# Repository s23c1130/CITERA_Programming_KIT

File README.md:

# CITERA Programming KIT
このプロジェクトは、千葉工業大学 電子工学研究会 (CITERA)で開発・頒布されたプログラミングキットの説明書・プログラミングツール・書き込みツール等をまとめたものです。

質問などは下のGoogle Formをご利用ください<BR>
https://forms.gle/aoQnFYQyJ1tKQqx78

バグの報告や機能の追加の希望等は上のGoogle Formをご利用いただくか、Issueを立ち上げてください。

**自己責任で導入を行ってください**<BR>

## 使用できる環境・推奨環境
このプログラムは次の環境で動作確認されています。
- Windows 11 (24H2)

最低限必要な環境は以下の通りです。
- Windows 11

必須ソフトとして.NET Framework 4.8が必要です。（Windows 11には初期状態で含まれています。）
.NET Framework 4.8 が入っていない環境の場合、下のリンクから、ランタイムをダウンロード・インストールしてください。

https://dotnet.microsoft.com/ja-jp/download/dotnet-framework/net48

（Windows 7以降の環境であれば動作すると思われますが、OSサポート終了のため推奨しません）

## プログラミング・書き込みツールの導入方法
ダウンロードしてから展開するだけでプログラミング・書き込みできるようになるReleaseファイルを配布しています。

矢印の先にReleasesがあります。これをクリックします。

Assetsにある`CITERA_Program_X.X.X.zip`をクリックし、ダウンロードします。

エクスプローラーの標準機能や7-Zip等のソフトを用いてZIPファイルを展開してください。

Windows エクスプローラーの標準機能を利用している場合は、展開ボタンを押してください。このとき、展開先のパスに2バイト文字（ひらがなや漢字などの日本語文字）が入っていないことを確認してください。（外部ツールの仕様により正常に動作しなくなります）

展開が完了すると次のような画面になります。

`CITERA_Programming_Kit_CWriter`にはマイコンに書き込むためのプログラムが入っています。<BR>
`BlocklyDuino-v2`にはプログラミングツールが入っています。

次にドライバの書き換えに進んでください。

## ドライバの書き換え
**この作業は管理者権限が必要です**<BR>
**Zadigは手順を間違えるとPCが不調になったりします。必ずこの手順通りに行ってください**<BR>

プログラムをマイコンに書き込む時、ドライバを書き換える必要があります。

準備中...

## プログラミングツールの説明
プログラミングツールの起動の仕方

まず、BlocklyDuino-v2のフォルダをダブルクリックで開いてください。

「index.html」もしくは「index」をダブルクリックで開いてください。
もし、使用するソフトウェアを聞かれた場合、「Microsoft Edge」もしくは「Google Chrome」を選択してください。

使用するボードの選択をするために、丸の箇所をクリックしてボードリストを開きます。

使用するボードはリストの下にあるので、下にスクロールします。

丸の箇所をクリックして「citera_board」を選択します。

ボードの選択後、BlocklyDuino-v2の表示の更新をします。

正常にボードの選択が出来た場合。表示の更新後、左側のツールボックスはこのような表示になります。「Arduino」等のツールボックスが表示されている場合、ボードの選択が正常に出来ていません。再度、ボードの選択をしてください。選択が完了している場合、以下のように、「citera_board」が黄色にハイライトされます。

プログラミングの例：3分タイマー

## 書き込みツールの説明
PCからマイコンボードにプログラムを書き込む方法について説明します。

1. マイコンボードとPCをUSBケーブルで接続します。
2. 電源をONにして、WRITEモードにスイッチをスライドさせます。
3. RESETボタンを押します。（画像では赤いボタンがリセットボタン）

これでマイコンボードは書き込みモードになりました。

次に、プログラムを書き込みます。

`CITERA_Programming_KIT_CWriter`フォルダを開きます

`CH32V203_USB_CBT.exe`(または`CH32V203_USB_CBT`)を実行してください。

## ライセンス
各ツール・設計図のライセンスについては、各フォルダに含まれている`README.md`をご参照ください。

`ProgrammingKit_回路図.pdf`<BR>
`ProgrammingKit_DotMatrix_回路図.pdf`<BR>
`ProgrammingKit_Car_回路図.pdf`<BR>
の著作権は CITERA また 23C1130 が保持しています。また、この回路図データは Creative Commons Attribution 4.0 International (CC BY 4.0) ライセンスの下で提供されています。
https://creativecommons.org/licenses/by/4.0/

## 外部ツールについて
### Zadig
このプロジェクトにはUSBドライバインストールツール Zadigを使用しています。<BR>
またReleaseにバイナリファイル（実行ファイル）が同梱されています。<BR>
- ライセンス:GPLv3
- ソースコード:https://github.com/pbatard/libwdi
- 公式HP:https://zadig.akeo.ie/

ZadigはGPLv3ライセンスの条件に基づいて再配布されています。<BR>
詳しくは`LICENSE/GPL-3.0.txt`をご参照ください。
### wchisp
このプロジェクトにはWCH ISP Tool wchispを使用しています。<BR>
またReleaseにバイナリファイル（実行ファイル）が同梱されています。<BR>
- ライセンス:GPLv2
- ソースコード:https://github.com/ch32-rs/wchisp
- バイナリコード配布先:https://github.com/ch32-rs/wchisp/releases/

wchispはGPLv2ライセンスの条件に基づいて再配布されています。<BR>
詳しくは`LICENSE/GPL-2.0.txt`をご参照ください。

### xPack RISC-V Embedded GCC
このプロジェクトにはxPack GNU RISC-V Embedded GCCを使用しています。<BR>
またReleaseにバイナリファイル（実行ファイル）が同梱されています。<BR>
- ライセンス:GPLv3 with Runtime Exception + MITライセンス
- ソースコード:https://github.com/openwch/risc-none-embed-gcc
- バイナリコード配布先:https://github.com/openwch/risc-none-embed-gcc/releases

xPack GNU RISC-V Embedded GCCはMITライセンスの条件に基づいて再配布されています。<BR>
詳しくは`LICENSE/MIT.txt`をご参照ください。
また、GPLv3 with Runtime Exceptionの条件に基づいて再配布されています。<BR>
詳しくは`LICENSE/gcc-exception-3.1.txt`をご参照ください。

### BusyBox-w32
このプロジェクトにはBusyBox-w32を使用しています。<BR>
またReleaseにバイナリファイル（実行ファイル）が同梱されています。<BR>
- ライセンス:GPLv2
- ソースコード:https://github.com/rmyorston/busybox-w32
- 公式HP:https://frippery.org/busybox/

BusyBox-w32はGPLv2ライセンスの条件に基づいて再配布されています。<BR>
詳しくは`LICENSE/GPL-2.0.txt`をご参照ください。

### GNU Make
このプロジェクトにはGNU makeを使用しています。<BR>
またReleaseにバイナリファイル（実行ファイル）が同梱されています。<BR>
- ライセンス:GPLv3
- ソースコード入手先/公式HP:https://www.gnu.org/software/make/

GNU MakeはGPLv2ライセンスの条件に基づいて再配布されています。<BR>
詳しくは`LICENSE/GPL-3.0.txt`をご参照ください。

これらのソフトウェアの開発者に感謝いたします。

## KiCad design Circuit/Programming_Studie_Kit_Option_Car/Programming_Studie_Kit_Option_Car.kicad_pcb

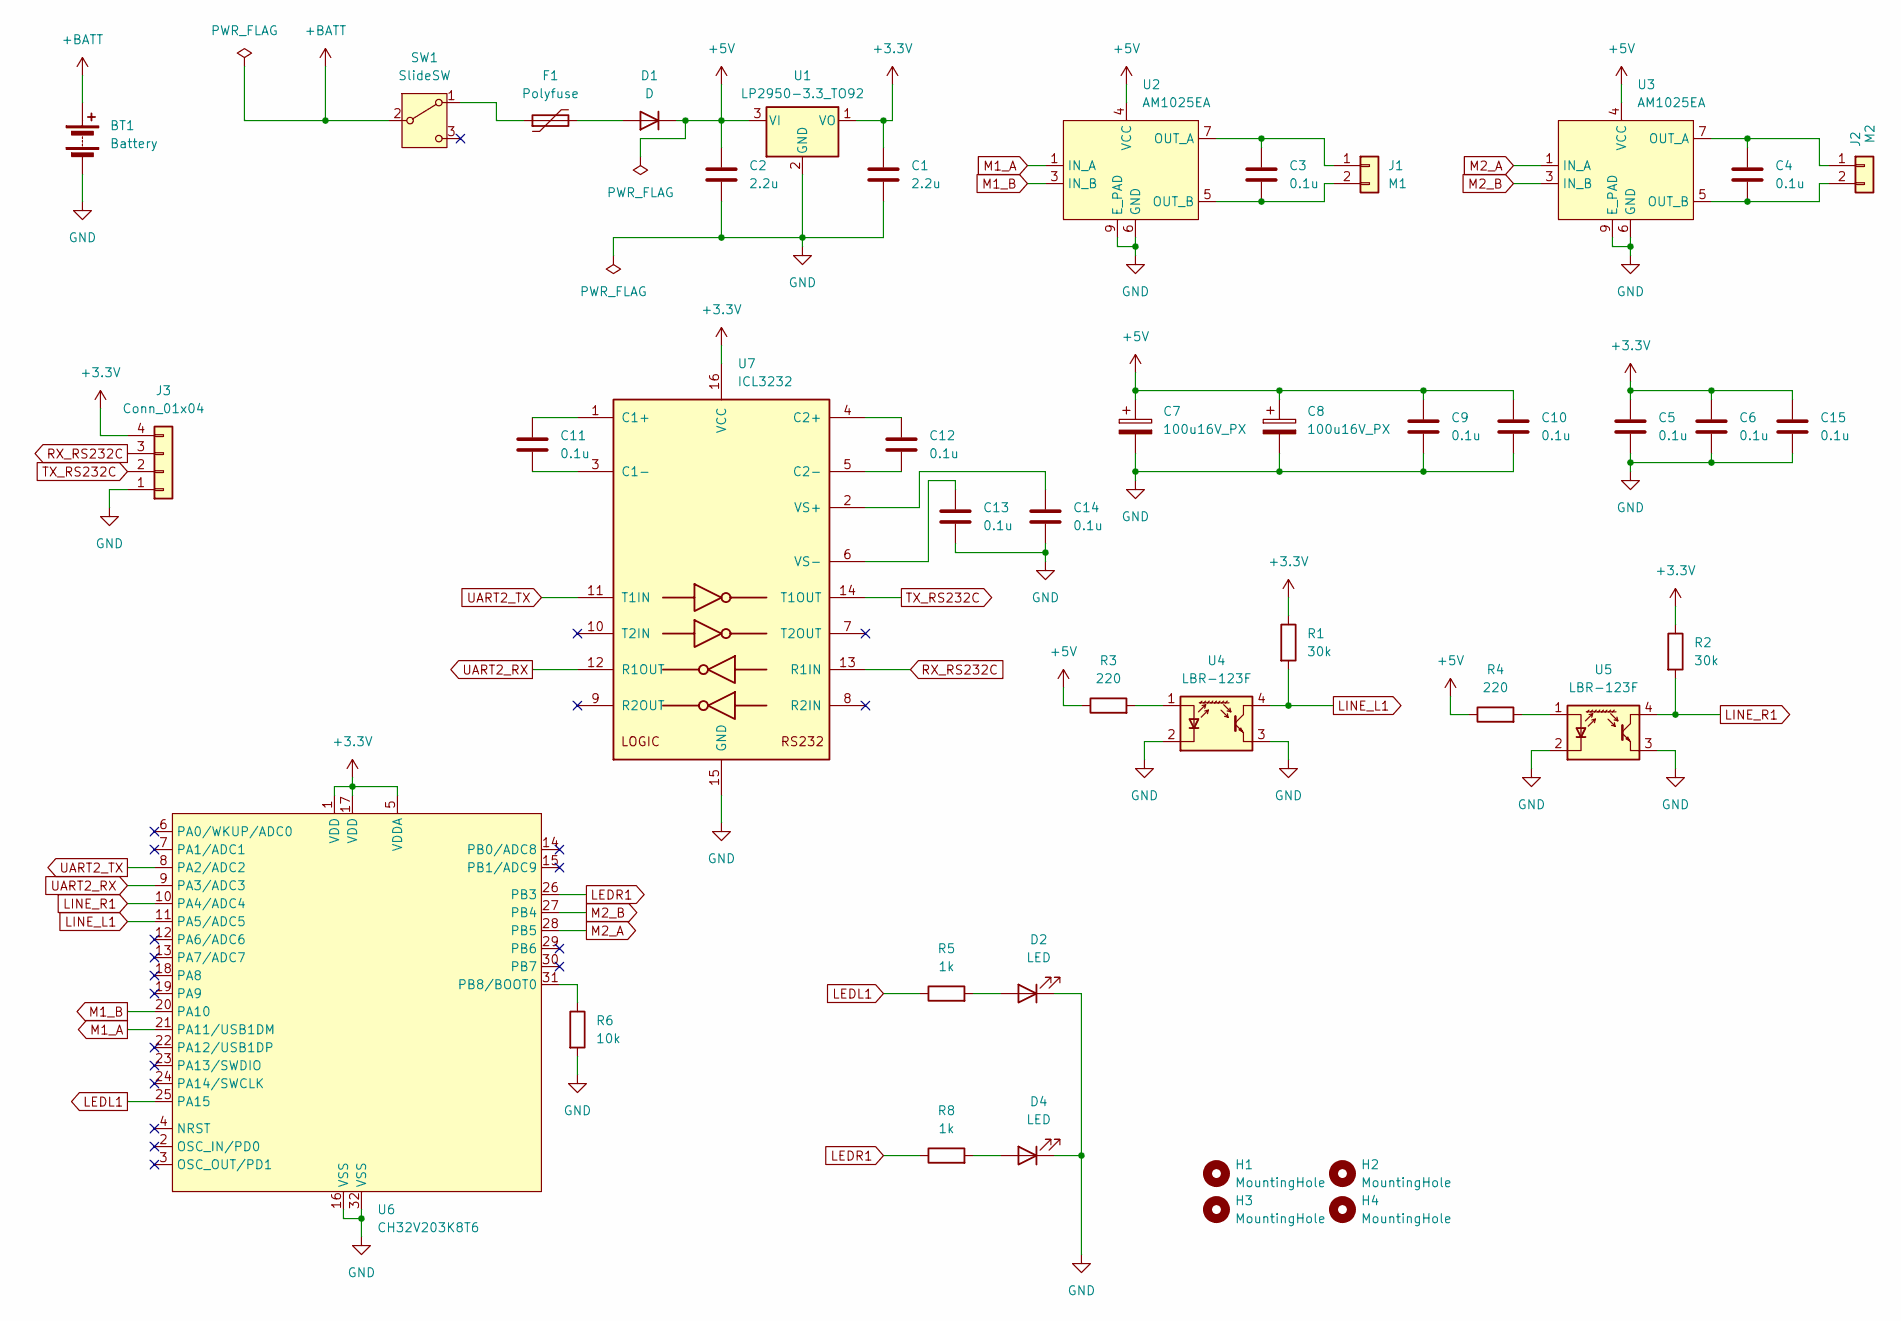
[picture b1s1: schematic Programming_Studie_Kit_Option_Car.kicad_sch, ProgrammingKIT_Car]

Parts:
BT1: Battery; JST_XH_B2B-XH-A_1x02_P2.50mm_Vertical
C1, C2: 2.2u; C_0603_1608Metric_Pad1.08x0.95mm_HandSolder
C3, C4, C5, C6, C9, C10, C11, C12, C13, C14, C15: 0.1u; C_0603_1608Metric_Pad1.08x0.95mm_HandSolder
C7, C8: 100u16V_PX; C_Radial_D5.0mm_H11.0mm_P2.00mm
D1: D; D_DO-41_SOD81_P5.08mm_Vertical_KathodeUp
D2, D4: LED; LED_D3.0mm
F1: Polyfuse; R_1_6W
H1, H2, H3, H4: MountingHole; MountingHole_3.2mm_M3
J1: M1; JST_XH_B2B-XH-A_1x02_P2.50mm_Vertical
J2: M2; JST_XH_B2B-XH-A_1x02_P2.50mm_Vertical
J3: Conn_01x04; JST_PH_B4B-PH-K_1x04_P2.00mm_Vertical
R1, R2: 30k; R_0603_1608Metric_Pad0.98x0.95mm_HandSolder
R3, R4: 220; R_0603_1608Metric_Pad0.98x0.95mm_HandSolder
R5, R8: 1k; R_0603_1608Metric_Pad0.98x0.95mm_HandSolder
R6: 10k; R_0603_1608Metric_Pad0.98x0.95mm_HandSolder
SW1: SlideSW; SW_SlideSW_3Pin_P2.54
U1: LP2950-3.3_TO92; TO-92_Inline
U2, U3: AM1025EA; SOP-8_3.76x4.96mm_P1.27mm_ThermalPAD
U4, U5: LBR-123F
U6: CH32V203K8T6; LQFP-32_7x7mm_P0.8mm
U7: ICL3232; TSSOP-16_4.4x5mm_P0.65mm

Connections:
+3.3V: C1.1, C5.1, C6.1, C15.1, J3.4, R1.1, R2.1, U1.1 (VO), U6.1 (VDD), U6.5 (VDDA), U6.17 (VDD), U7.16 (VCC)
+5V: C2.1, C7.1, C8.1, C9.1, C10.1, D1.1 (K), R3.1, R4.1, U1.3 (VI), U2.4 (VCC), U3.4 (VCC)
+BATT: BT1.1 (+), SW1.2 (B)
GND: BT1.2 (-), C1.2, C2.2, C5.2, C6.2, C7.2, C8.2, C9.2, C10.2, C13.2, C14.2, C15.2, D2.1 (K), D4.1 (K), J3.1, R6.2, U1.2 (GND), U2.6 (GND), U2.9 (E_PAD), U3.6 (GND), U3.9 (E_PAD), U4.2 (K), U4.3 (E), U5.2 (K), U5.3 (E), U6.16 (VSS), U6.32 (VSS), U7.15 (GND)
LEDL1: R5.1, U6.25 (PA15)
LEDR1: R8.1, U6.26 (PB3)
LINE_L1: R1.2, U4.4 (C), U6.11 (PA5/ADC5)
LINE_R1: R2.2, U5.4 (C), U6.10 (PA4/ADC4)
M1_A: U2.1 (IN_A), U6.21 (PA11/USB1DM)
M1_B: U2.3 (IN_B), U6.20 (PA10)
M2_A: U3.1 (IN_A), U6.28 (PB5)
M2_B: U3.3 (IN_B), U6.27 (PB4)
unnamed: D1.2 (A), F1.2
unnamed: D2.2 (A), R5.2
unnamed: D4.2 (A), R8.2
unnamed: C3.1, J1.1, U2.7 (OUT_A)
unnamed: C3.2, J1.2, U2.5 (OUT_B)
unnamed: C4.1, J2.1, U3.7 (OUT_A)
unnamed: C4.2, J2.2, U3.5 (OUT_B)
unnamed: F1.1, SW1.1 (A)
unnamed: R3.2, U4.1 (A)
unnamed: R4.2, U5.1 (A)
unnamed: R6.1, U6.31 (PB8/BOOT0)
unnamed: C11.1, U7.1 (C1+)
unnamed: C11.2, U7.3 (C1-)
unnamed: C12.1, U7.4 (C2+)
unnamed: C12.2, U7.5 (C2-)
unnamed: C14.1, U7.2 (VS+)
unnamed: C13.1, U7.6 (VS-)
RX_RS232C: J3.3, U7.13 (R1IN)
TX_RS232C: J3.2, U7.14 (T1OUT)
UART2_RX: U6.9 (PA3/ADC3), U7.12 (R1OUT)
UART2_TX: U6.8 (PA2/ADC2), U7.11 (T1IN)

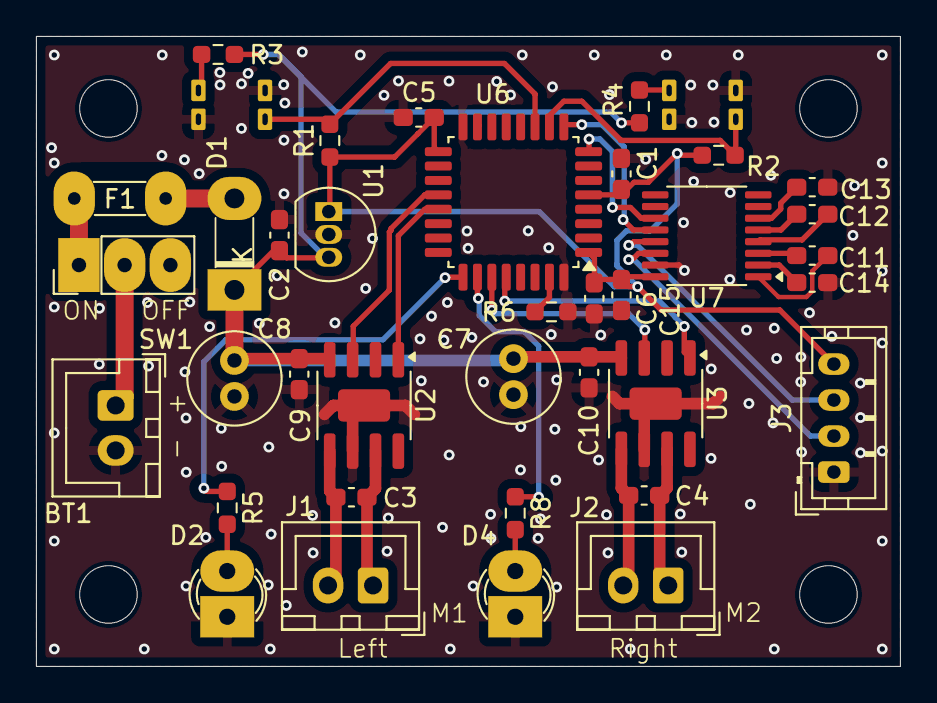
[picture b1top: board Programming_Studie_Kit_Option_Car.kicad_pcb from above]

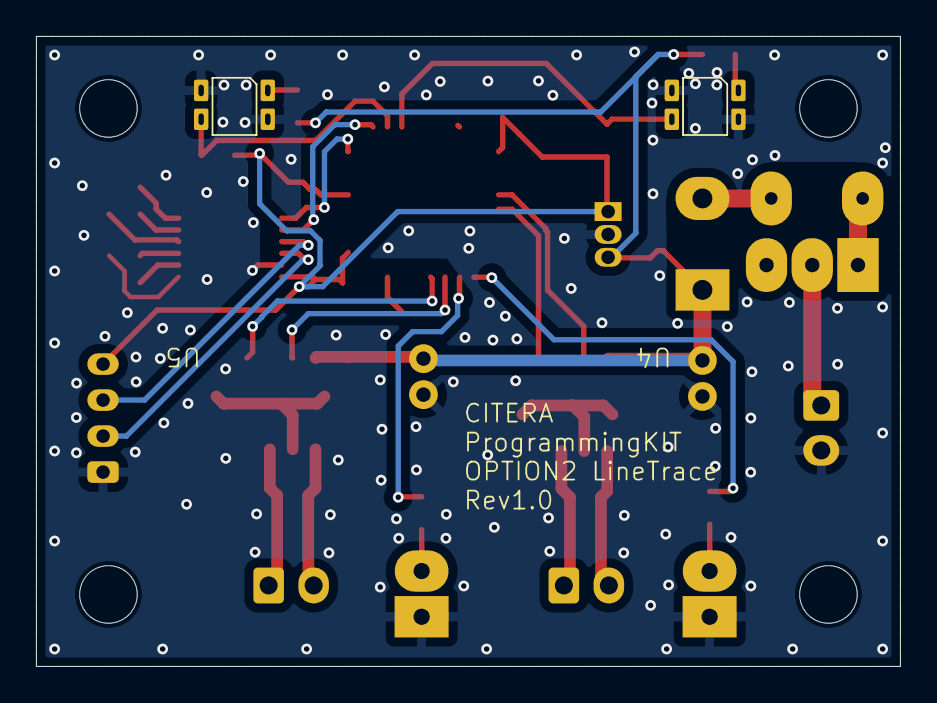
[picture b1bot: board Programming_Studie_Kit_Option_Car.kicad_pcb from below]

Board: 2 copper layers, 48.0 x 35.0 mm, 42 parts (2 on the bottom side), 33 nets.

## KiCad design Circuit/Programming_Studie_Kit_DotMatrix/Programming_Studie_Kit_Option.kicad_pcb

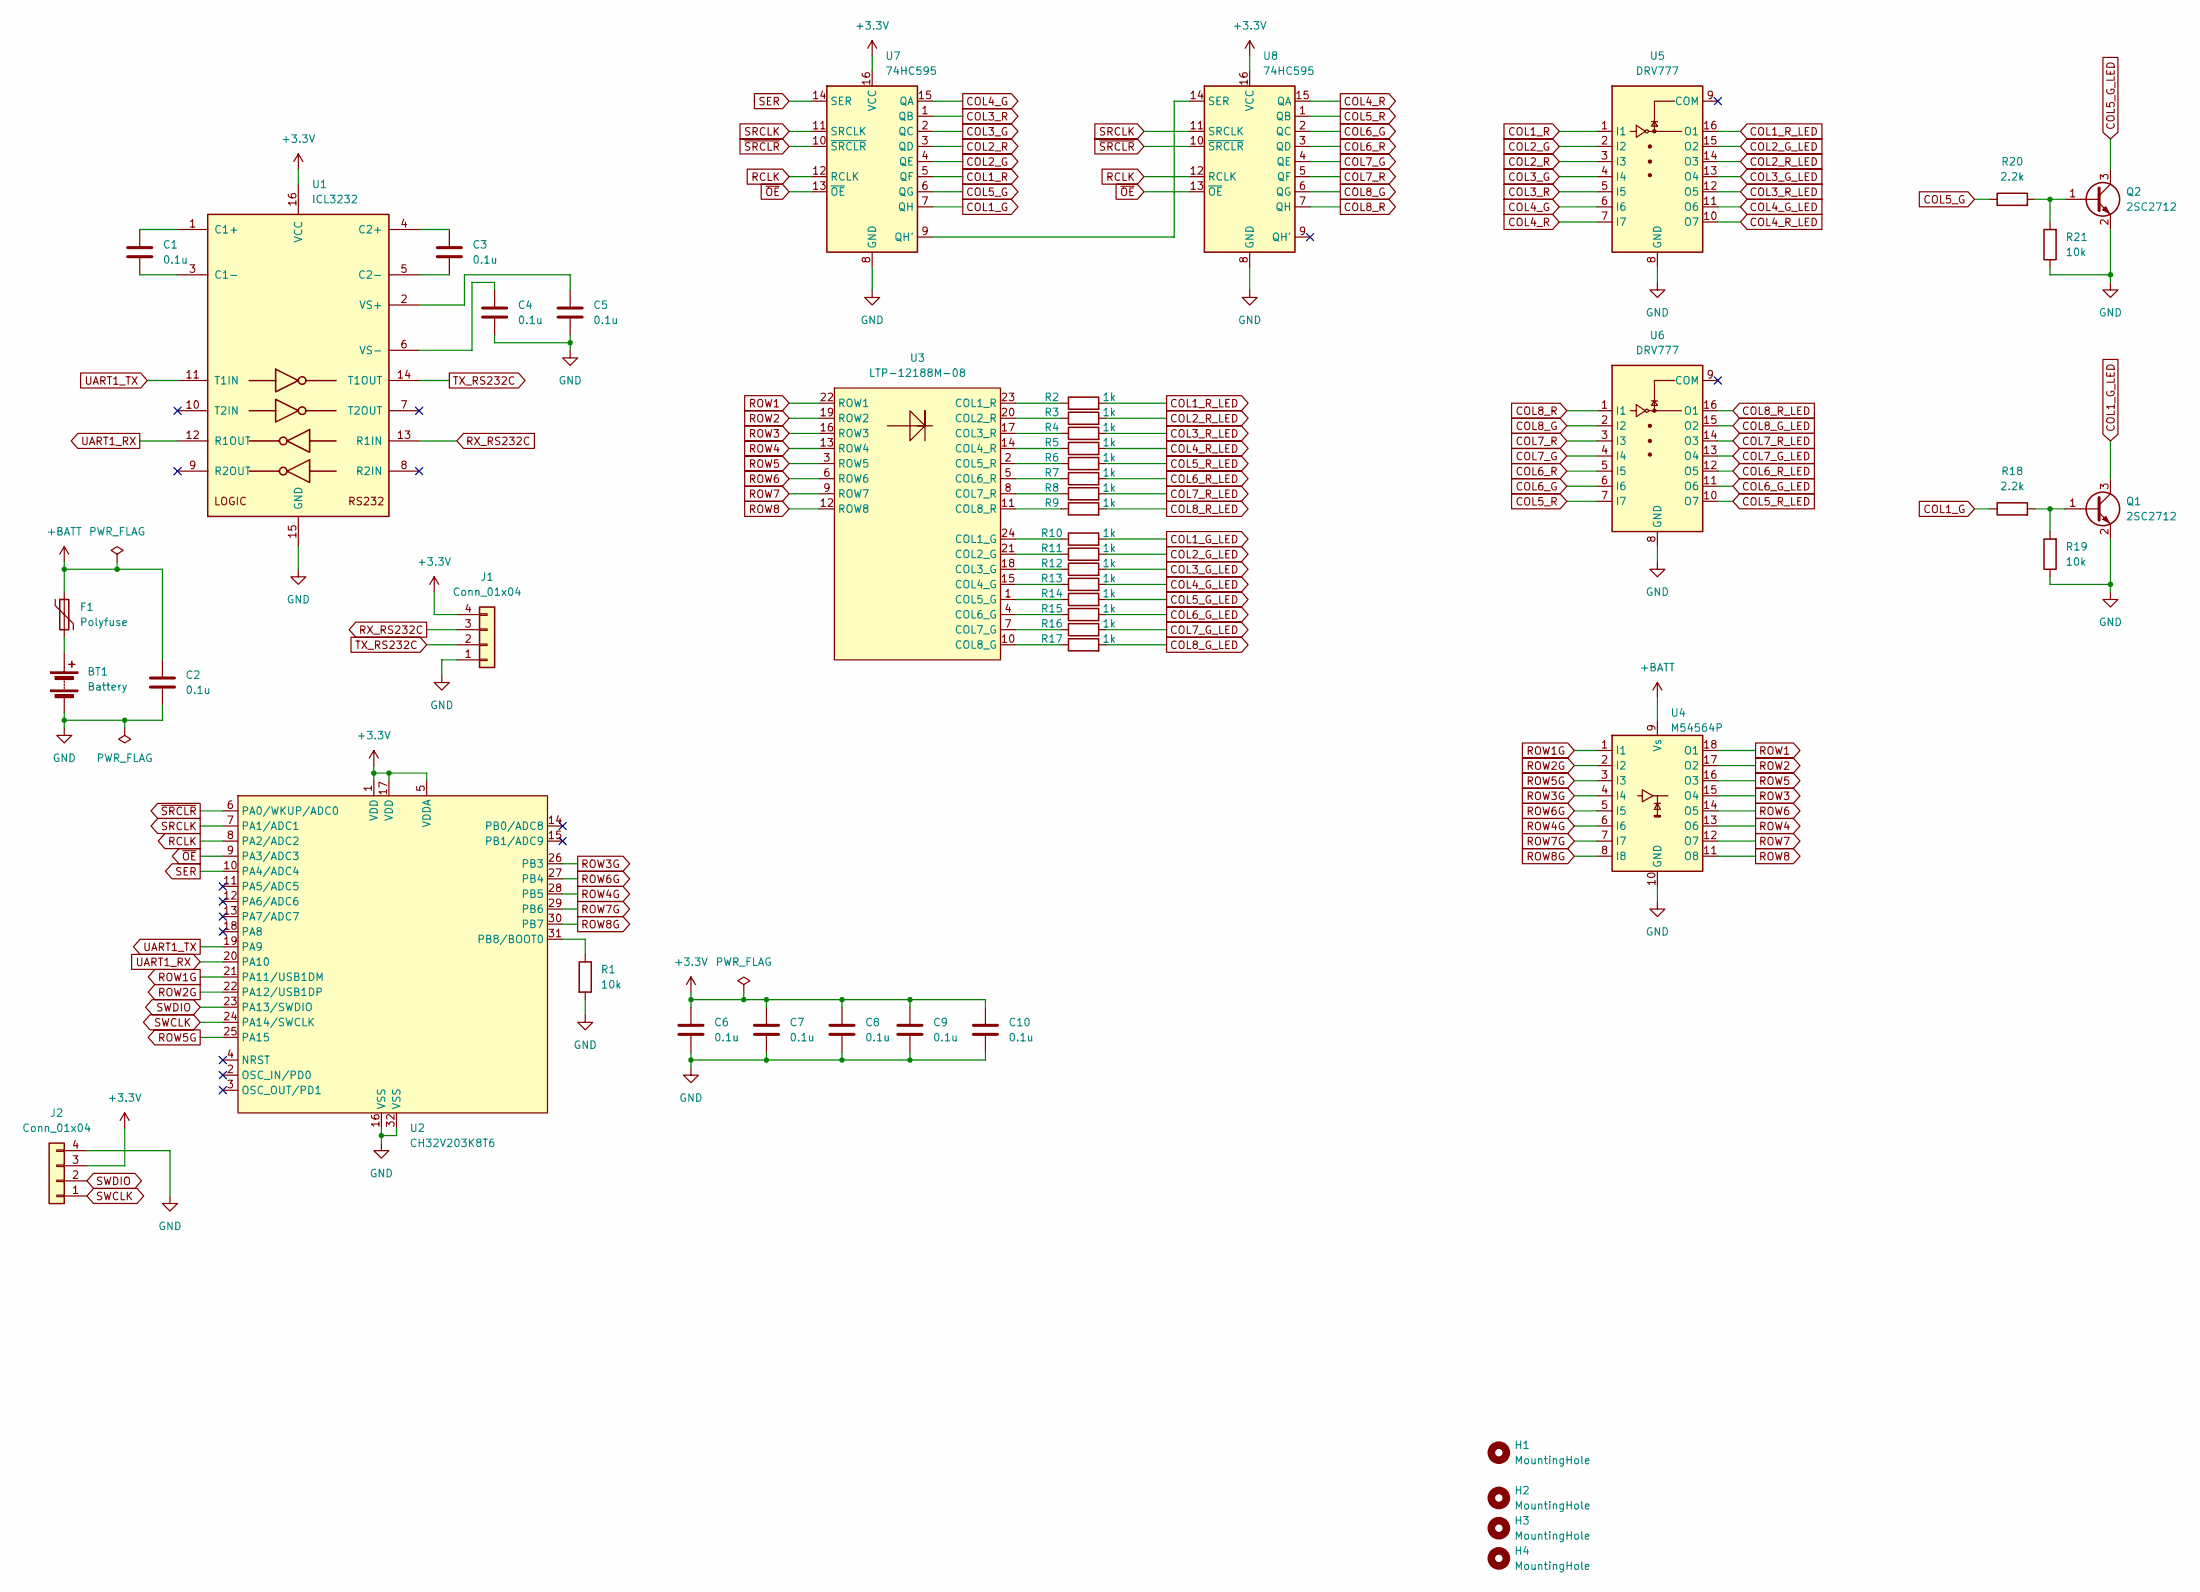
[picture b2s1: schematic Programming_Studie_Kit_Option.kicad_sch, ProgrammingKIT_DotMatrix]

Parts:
BT1: Battery; JST_XH_B2B-XH-A_1x02_P2.50mm_Vertical
C1, C2, C3, C4, C5, C6, C7, C8, C9, C10: 0.1u; C_0603_1608Metric_Pad1.08x0.95mm_HandSolder
F1: Polyfuse; R_1_6W
H1, H2, H3, H4: MountingHole; MountingHole_3.2mm_M3
J1: Conn_01x04; JST_PH_B4B-PH-K_1x04_P2.00mm_Vertical
J2: Conn_01x04; PinHeader_1x04_Program
Q1, Q2: 2SC2712; SOT-23-3
R1, R19, R21: 10k; R_0603_1608Metric_Pad0.98x0.95mm_HandSolder
R2, R3, R4, R5, R6, R7, R8, R9, R10, R11, R12, R13, R14, R15, R16, R17: 1k; R_0603_1608Metric_Pad0.98x0.95mm_HandSolder
R18, R20: 2.2k; R_0603_1608Metric_Pad0.98x0.95mm_HandSolder
U1: ICL3232; TSSOP-16_4.4x5mm_P0.65mm
U2: CH32V203K8T6; LQFP-32_7x7mm_P0.8mm
U3: LTP-12188M-08
U4: M54564P; DIP-18_W7.62mm_LongPads
U5, U6: DRV777; SOIC-16_3.9x9.9mm_P1.27mm
U7, U8: 74HC595; SOP-16_4.55x10.3mm_P1.27mm

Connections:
+3.3V: C6.1, C7.1, C8.1, C9.1, C10.1, J1.4, J2.3, U1.16 (VCC), U2.1 (VDD), U2.5 (VDDA), U2.17 (VDD), U7.16 (VCC), U8.16 (VCC)
+BATT: C2.1, F1.1, U4.9 (Vs)
COL1_G: R18.1, U7.7 (QH)
COL1_G_LED: Q1.3 (C), R10.2
COL1_R: U5.1 (I1), U7.5 (QF)
COL1_R_LED: R2.2, U5.16 (O1)
COL2_G: U5.2 (I2), U7.4 (QE)
COL2_G_LED: R11.2, U5.15 (O2)
COL2_R: U5.3 (I3), U7.3 (QD)
COL2_R_LED: R3.2, U5.14 (O3)
COL3_G: U5.4 (I4), U7.2 (QC)
COL3_G_LED: R12.2, U5.13 (O4)
COL3_R: U5.5 (I5), U7.1 (QB)
COL3_R_LED: R4.2, U5.12 (O5)
COL4_G: U5.6 (I6), U7.15 (QA)
COL4_G_LED: R13.2, U5.11 (O6)
COL4_R: U5.7 (I7), U8.15 (QA)
COL4_R_LED: R5.2, U5.10 (O7)
COL5_G: R20.1, U7.6 (QG)
COL5_G_LED: Q2.3 (C), R14.2
COL5_R: U6.7 (I7), U8.1 (QB)
COL5_R_LED: R6.2, U6.10 (O7)
COL6_G: U6.6 (I6), U8.2 (QC)
COL6_G_LED: R15.2, U6.11 (O6)
COL6_R: U6.5 (I5), U8.3 (QD)
COL6_R_LED: R7.2, U6.12 (O5)
COL7_G: U6.4 (I4), U8.4 (QE)
COL7_G_LED: R16.2, U6.13 (O4)
COL7_R: U6.3 (I3), U8.5 (QF)
COL7_R_LED: R8.2, U6.14 (O3)
COL8_G: U6.2 (I2), U8.6 (QG)
COL8_G_LED: R17.2, U6.15 (O2)
COL8_R: U6.1 (I1), U8.7 (QH)
COL8_R_LED: R9.2, U6.16 (O1)
GND: BT1.2 (-), C2.2, C4.2, C5.2, C6.2, C7.2, C8.2, C9.2, C10.2, J1.1, J2.4, Q1.2 (E), Q2.2 (E), R1.2, R19.1, R21.1, U1.15 (GND), U2.16 (VSS), U2.32 (VSS), U4.10 (GND), U5.8 (GND), U6.8 (GND), U7.8 (GND), U8.8 (GND)
unnamed: BT1.1 (+), F1.2
unnamed: Q1.1 (B), R18.2, R19.2
unnamed: Q2.1 (B), R20.2, R21.2
unnamed: C1.1, U1.1 (C1+)
unnamed: C1.2, U1.3 (C1-)
unnamed: C3.1, U1.4 (C2+)
unnamed: C3.2, U1.5 (C2-)
unnamed: C5.1, U1.2 (VS+)
unnamed: C4.1, U1.6 (VS-)
unnamed: R1.1, U2.31 (PB8/BOOT0)
unnamed: R10.1, U3.24 (COL1_G)
unnamed: R2.1, U3.23 (COL1_R)
unnamed: R11.1, U3.21 (COL2_G)
unnamed: R3.1, U3.20 (COL2_R)
unnamed: R12.1, U3.18 (COL3_G)
unnamed: R4.1, U3.17 (COL3_R)
unnamed: R13.1, U3.15 (COL4_G)
unnamed: R5.1, U3.14 (COL4_R)
unnamed: R14.1, U3.1 (COL5_G)
unnamed: R6.1, U3.2 (COL5_R)
unnamed: R15.1, U3.4 (COL6_G)
unnamed: R7.1, U3.5 (COL6_R)
unnamed: R16.1, U3.7 (COL7_G)
unnamed: R8.1, U3.8 (COL7_R)
unnamed: R17.1, U3.10 (COL8_G)
unnamed: R9.1, U3.11 (COL8_R)
unnamed: U7.9 (QH'), U8.14 (SER)
RCLK: U2.8 (PA2/ADC2), U7.12 (RCLK), U8.12 (RCLK)
ROW1: U3.22 (ROW1), U4.18 (O1)
ROW1G: U2.21 (PA11/USB1DM), U4.1 (I1)
ROW2: U3.19 (ROW2), U4.17 (O2)
ROW2G: U2.22 (PA12/USB1DP), U4.2 (I2)
ROW3: U3.16 (ROW3), U4.15 (O4)
ROW3G: U2.26 (PB3), U4.4 (I4)
ROW4: U3.13 (ROW4), U4.13 (O6)
ROW4G: U2.28 (PB5), U4.6 (I6)
ROW5: U3.3 (ROW5), U4.16 (O3)
ROW5G: U2.25 (PA15), U4.3 (I3)
ROW6: U3.6 (ROW6), U4.14 (O5)
ROW6G: U2.27 (PB4), U4.5 (I5)
ROW7: U3.9 (ROW7), U4.12 (O7)
ROW7G: U2.29 (PB6), U4.7 (I7)
ROW8: U3.12 (ROW8), U4.11 (O8)
ROW8G: U2.30 (PB7), U4.8 (I8)
RX_RS232C: J1.3, U1.13 (R1IN)
SER: U2.10 (PA4/ADC4), U7.14 (SER)
SRCLK: U2.7 (PA1/ADC1), U7.11 (SRCLK), U8.11 (SRCLK)
SWCLK: J2.1, U2.24 (PA14/SWCLK)
SWDIO: J2.2, U2.23 (PA13/SWDIO)
TX_RS232C: J1.2, U1.14 (T1OUT)
UART1_RX: U1.12 (R1OUT), U2.20 (PA10)
UART1_TX: U1.11 (T1IN), U2.19 (PA9)
~OE: U2.9 (PA3/ADC3), U7.13 (~OE), U8.13 (~OE)
~SRCLR: U2.6 (PA0/WKUP/ADC0), U7.10 (~SRCLR), U8.10 (~SRCLR)

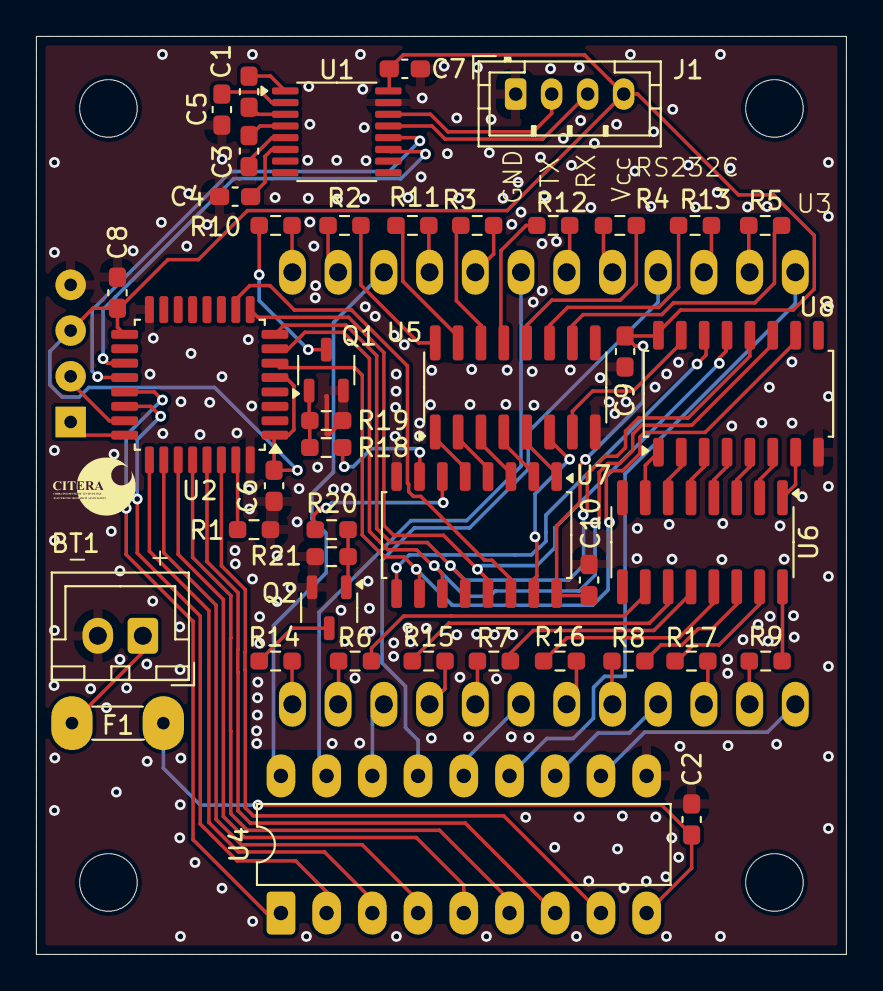
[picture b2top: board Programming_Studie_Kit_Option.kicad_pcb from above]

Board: 2 copper layers, 45.0 x 51.0 mm, 49 parts (1 on the bottom side), 89 nets.

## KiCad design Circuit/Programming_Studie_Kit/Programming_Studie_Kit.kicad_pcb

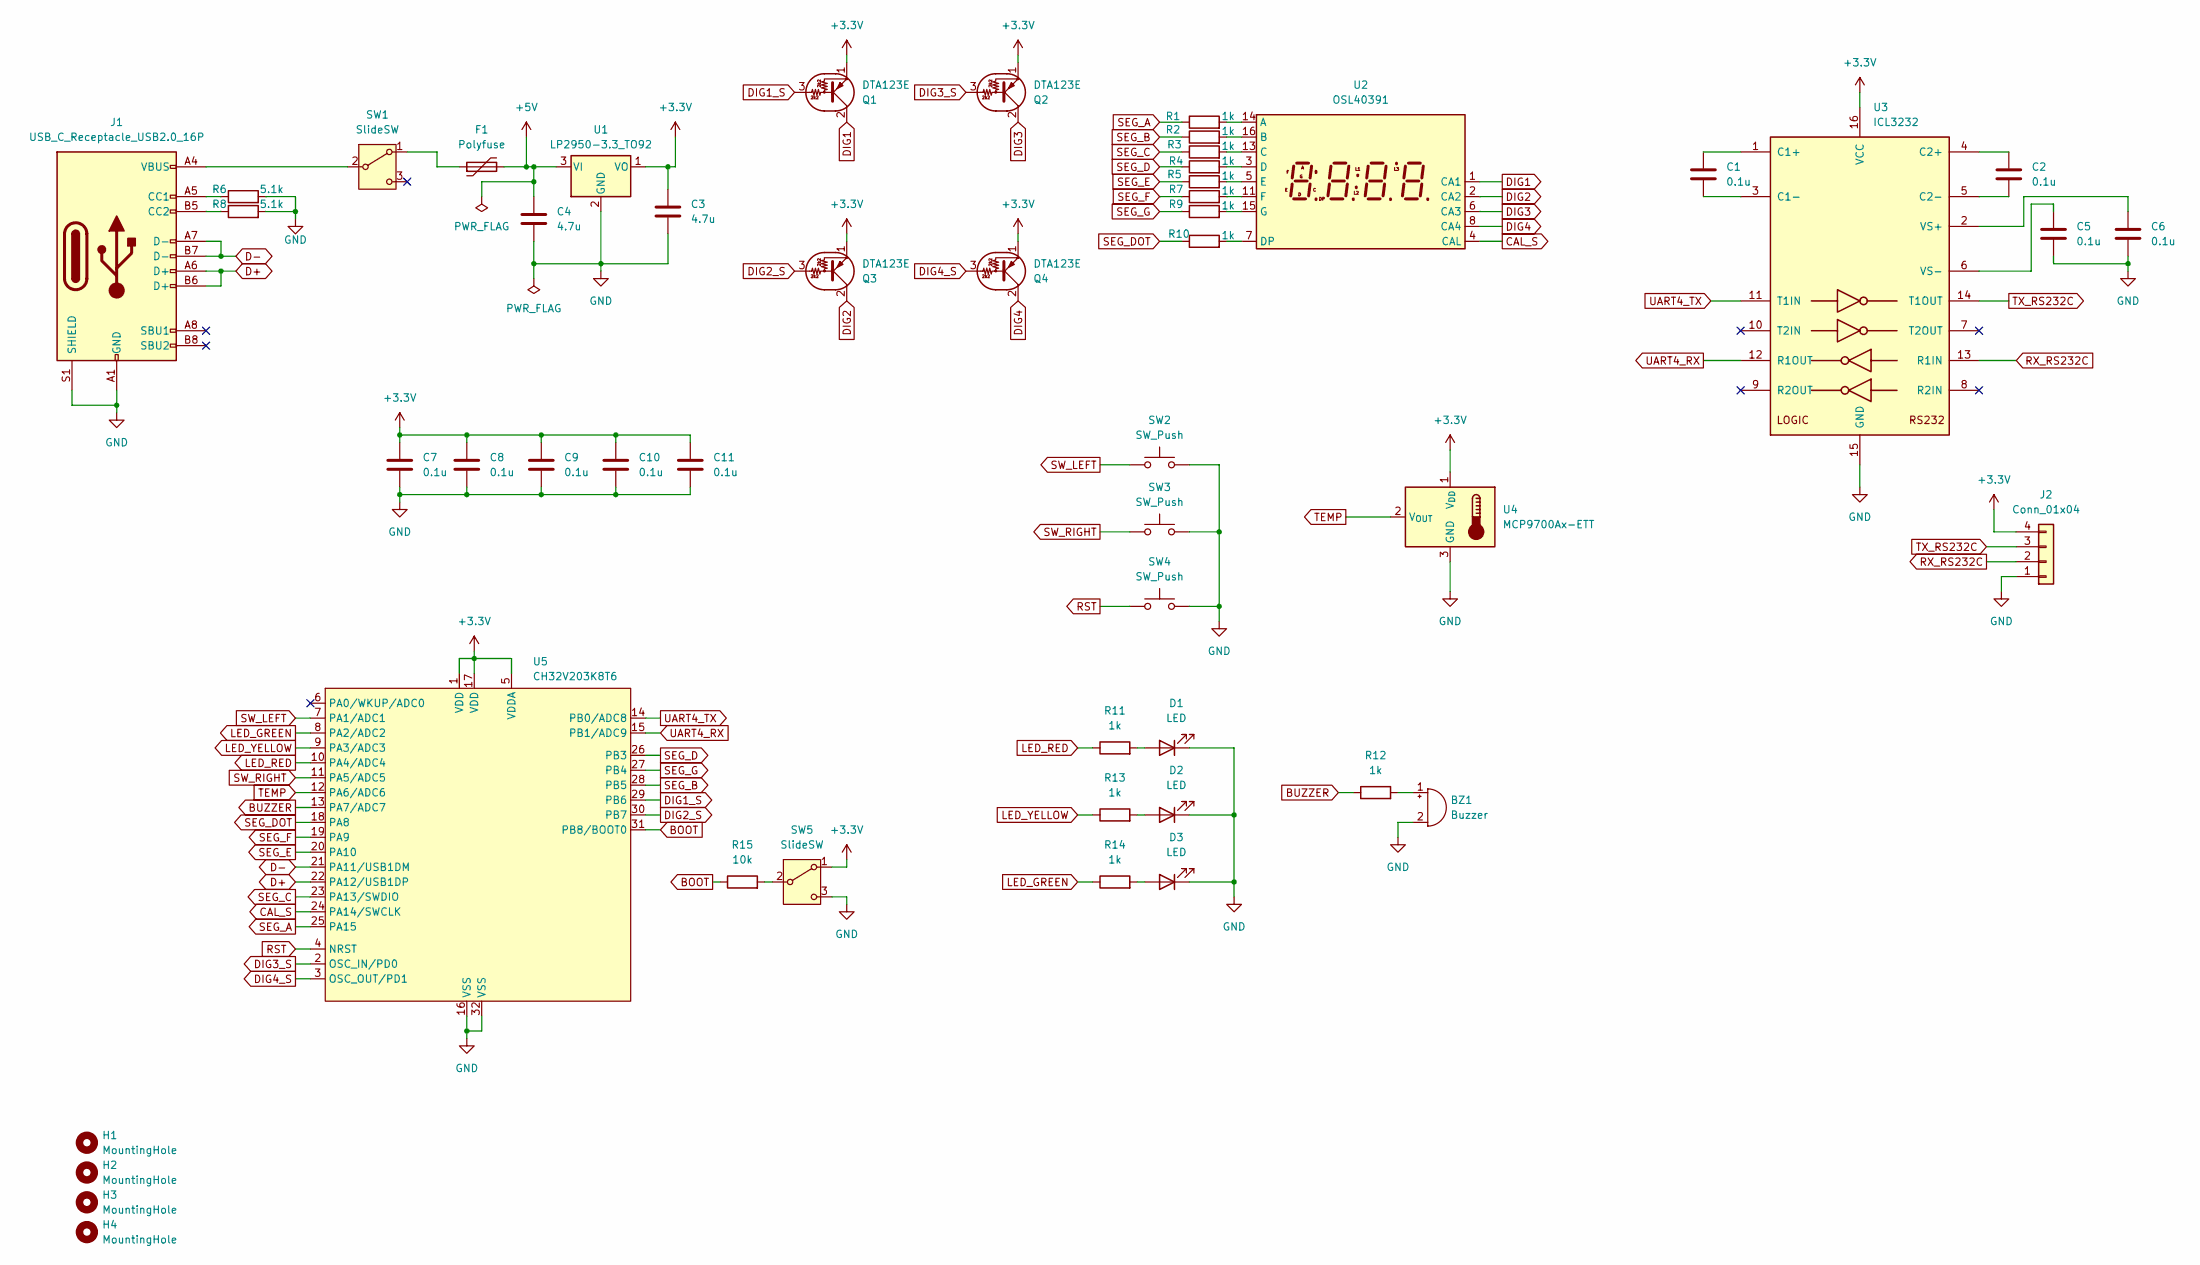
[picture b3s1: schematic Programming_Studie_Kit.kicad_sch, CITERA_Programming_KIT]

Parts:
BZ1: Buzzer; AKI_CERAMIC_BUZZER_PKM13EPYH4000-A0
C1, C2, C5, C6, C7, C8, C9, C10, C11: 0.1u; C_0603_1608Metric_Pad1.08x0.95mm_HandSolder
C3, C4: 4.7u; C_0603_1608Metric_Pad1.08x0.95mm_HandSolder
D1, D2, D3: LED; LED_D3.0mm
F1: Polyfuse; R_1_6W
H1, H2, H3, H4: MountingHole; MountingHole_3.2mm_M3
J1: USB_C_Receptacle_USB2.0_16P; USB_C_YTC-TC16-473
J2: Conn_01x04; JST_PH_B4B-PH-K_1x04_P2.00mm_Vertical
Q1, Q2, Q3, Q4: DTA123E; TO-92_Inline
R1, R2, R3, R4, R5, R7, R9, R10, R11, R12, R13, R14: 1k; R_0603_1608Metric_Pad0.98x0.95mm_HandSolder
R6, R8: 5.1k; R_0603_1608Metric_Pad0.98x0.95mm_HandSolder
R15: 10k; R_0603_1608Metric_Pad0.98x0.95mm_HandSolder
SW1, SW5: SlideSW; SW_SlideSW_3Pin_P2.54
SW2, SW3, SW4: SW_Push; SW_PUSH_6mm
U1: LP2950-3.3_TO92; TO-92_Inline
U2: OSL40391
U3: ICL3232; TSSOP-16_4.4x5mm_P0.65mm
U4: MCP9700Ax-ETT; TO-92_Inline
U5: CH32V203K8T6; LQFP-32_7x7mm_P0.8mm

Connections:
+3.3V: C3.1, C7.1, C8.1, C9.1, C10.1, C11.1, J2.4, Q1.1 (E), Q2.1 (E), Q3.1 (E), Q4.1 (E), SW5.1 (A), U1.1 (VO), U3.16 (VCC), U4.1 (V_{DD}), U5.1 (VDD), U5.5 (VDDA), U5.17 (VDD)
+5V: C4.1, F1.2, U1.3 (VI)
BOOT: R15.1, U5.31 (PB8/BOOT0)
BUZZER: R12.1, U5.13 (PA7/ADC7)
CAL_S: U2.4 (CAL), U5.24 (PA14/SWCLK)
D+: J1.A6 (D+), J1.B6 (D+), U5.22 (PA12/USB1DP)
D-: J1.A7 (D-), J1.B7 (D-), U5.21 (PA11/USB1DM)
DIG1: Q1.2 (C), U2.1 (CA1)
DIG1_S: Q1.3 (B), U5.29 (PB6)
DIG2: Q3.2 (C), U2.2 (CA2)
DIG2_S: Q3.3 (B), U5.30 (PB7)
DIG3: Q2.2 (C), U2.6 (CA3)
DIG3_S: Q2.3 (B), U5.2 (OSC_IN/PD0)
DIG4: Q4.2 (C), U2.8 (CA4)
DIG4_S: Q4.3 (B), U5.3 (OSC_OUT/PD1)
GND: BZ1.2 (-), C3.2, C4.2, C5.2, C6.2, C7.2, C8.2, C9.2, C10.2, C11.2, D1.1 (K), D2.1 (K), D3.1 (K), J1.A1 (GND), J1.A12 (GND), J1.B1 (GND), J1.B12 (GND), J1.S1 (SHIELD), J2.1, R6.2, R8.2, SW2.2, SW3.2, SW4.2, SW5.3 (C), U1.2 (GND), U3.15 (GND), U4.3 (GND), U5.16 (VSS), U5.32 (VSS)
LED_GREEN: R14.1, U5.8 (PA2/ADC2)
LED_RED: R11.1, U5.10 (PA4/ADC4)
LED_YELLOW: R13.1, U5.9 (PA3/ADC3)
unnamed: BZ1.1 (+), R12.2
unnamed: D1.2 (A), R11.2
unnamed: D2.2 (A), R13.2
unnamed: D3.2 (A), R14.2
unnamed: J1.A5 (CC1), R6.1
unnamed: J1.B5 (CC2), R8.1
unnamed: F1.1, SW1.1 (A)
unnamed: J1.A4 (VBUS), J1.A9 (VBUS), J1.B4 (VBUS), J1.B9 (VBUS), SW1.2 (B)
unnamed: R15.2, SW5.2 (B)
unnamed: R1.2, U2.14 (A)
unnamed: R2.2, U2.16 (B)
unnamed: R3.2, U2.13 (C)
unnamed: R4.2, U2.3 (D)
unnamed: R10.2, U2.7 (DP)
unnamed: R5.2, U2.5 (E)
unnamed: R7.2, U2.11 (F)
unnamed: R9.2, U2.15 (G)
unnamed: C1.1, U3.1 (C1+)
unnamed: C1.2, U3.3 (C1-)
unnamed: C2.1, U3.4 (C2+)
unnamed: C2.2, U3.5 (C2-)
unnamed: C6.1, U3.2 (VS+)
unnamed: C5.1, U3.6 (VS-)
RST: SW4.1, U5.4 (NRST)
RX_RS232C: J2.2, U3.13 (R1IN)
SEG_A: R1.1, U5.25 (PA15)
SEG_B: R2.1, U5.28 (PB5)
SEG_C: R3.1, U5.23 (PA13/SWDIO)
SEG_D: R4.1, U5.26 (PB3)
SEG_DOT: R10.1, U5.18 (PA8)
SEG_E: R5.1, U5.20 (PA10)
SEG_F: R7.1, U5.19 (PA9)
SEG_G: R9.1, U5.27 (PB4)
SW_LEFT: SW2.1, U5.7 (PA1/ADC1)
SW_RIGHT: SW3.1, U5.11 (PA5/ADC5)
TEMP: U4.2 (V_{OUT}), U5.12 (PA6/ADC6)
TX_RS232C: J2.3, U3.14 (T1OUT)
UART4_RX: U3.12 (R1OUT), U5.15 (PB1/ADC9)
UART4_TX: U3.11 (T1IN), U5.14 (PB0/ADC8)

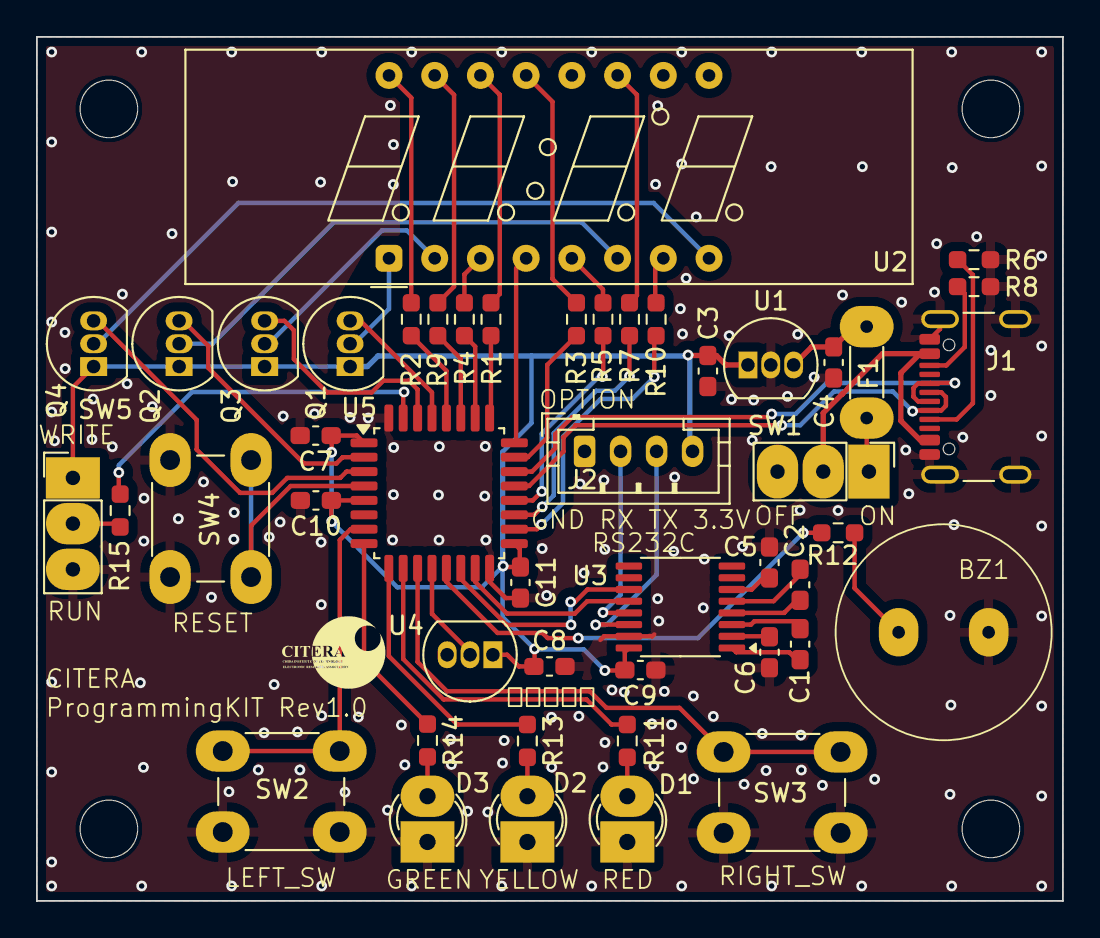
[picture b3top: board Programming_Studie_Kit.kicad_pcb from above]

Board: 2 copper layers, 57.0 x 48.0 mm, 51 parts (0 on the bottom side), 58 nets.

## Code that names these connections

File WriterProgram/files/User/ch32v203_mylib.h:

/*
 * ch32v203_mylib.h
 *
 *  Created on: Jun 30, 2024
 *      CITERA Programming KIT用システム
 *      
 */

#ifndef USER_CH32V203_MYLIB_H_
#define USER_CH32V203_MYLIB_H_

//ピン番号
#define PA0 0x10
#define PA1 0x11
#define PA2 0x12
#define PA3 0x13
#define PA4 0x14
#define PA5 0x15
#define PA6 0x16
#define PA7 0x17
#define PA8 0x18
#define PA9 0x19
#define PA10 0x1A
#define PA11 0x1B
#define PA12 0x1C
#define PA13 0x1D
#define PA14 0x1E
#define PA15 0x1F

#define PB0 0x20
#define PB1 0x21
#define PB3 0x23
#define PB4 0x24
#define PB5 0x25
#define PB6 0x26
#define PB7 0x27
#define PB8 0x28

#define PD0 0x40
#define PD1 0x41

//OUTPUT SPEED
#define OUTPUT_2MHz 0b10
#define OUTPUT_10MHz 0b01
#define OUTPUT_50MHz 0b11

//PINMODE
//0xQWER; Q:インプットかアウトプットか
//W:プルアップかプルダウンか(outputでは常に0)
//ER:CNFのビット
#define INPUT 0b1001
#define INPUT_PULLUP 0b1110
#define INPUT_PULLDOWN 0b1010
#define INPUT_ANALOG 0b1000
#define OUTPUT 0b0000
#define OUTPUT_OPENDRAIN 0b0001
#define OUTPUT_FUNC 0b0010
#define OUTPUT_OPENDRAIN_FUNC 0b0011

void GPIOA_init(void); //GPIOAのセットアップ
void GPIOB_init(void); //GPIOBのセットアップ
void GPIOC_init(void); //GPIOCのセットアップ
void GPIOD_init(void); //GPIODのセットアップ
int GPIO_output_speed(int speed); //GPIO OUTPUT時の速度指定
void pinMode(int Pin,int mode); //GPIO入出力設定
unsigned char digitalRead(int Pin); //GPIO入力
void digitalWrite(int Pin, int val); //GPIO出力
//ビット置き換え関数
uint32_t bit_replace(uint32_t data, uint32_t byte, uint8_t len, uint8_t shift);


////////////ここからCITERA編集///////////////////////////

#define SW_LEFT PA1
#define LED_GREEN PA2
#define LED_YELLOW PA3
#define LED_RED PA4
#define SW_RIGHT PA5
#define TEMP PA6
#define BUZZER PA7
#define SEG_DOT PA8
#define SEG_F PA9
#define SEG_E PA10
#define SEG_C PA13
#define CAL_S PA14
#define SEG_A PA15
#define DIG3 PD0
#define DIG4 PD1
#define UART4_TX PB0
#define UART4_RX PB1
#define SEG_D PB3
#define SEG_G PB4
#define SEG_B PB5
#define DIG1 PB6
#define DIG2 PB7

#define __DOT1 0x01
#define __DOT2 0x02
#define __DOT3 0x04
#define __DOT4 0x08
#define __CORON 0x10
#define __DASH 0x20

#define SOFT_UART_DELAY 15000 //9600bps
#define UART_TIMEOUT 5
#define MOTOR_DELAY 2
#define UART_MATRIX_DELAY 2

typedef struct{
    uint8_t red_data[8];
    uint8_t green_data[8];
}DotMatrix_t;

void Clock_init(void); //クロック設定 (144MHz)
void pinSetting(void); //ピン入出力設定
void ADC_Setting(void); //ADC設定
void UART_Setting(void); //UART設定
void ToneSetting(void); //Tone関数用タイマー設定
void TIM2_InterruptSetting(void); //TIM2 割り込み用設定

void tone(int freq);
void noTone(void);

void SerialWrite(uint8_t data);
int SerialRead(void);

void TIM2_IRQHandler (void) __attribute__ ((interrupt ("WCH-Interrupt-fast")));
void EXTI1_IRQHandler (void) __attribute__ ((interrupt ("WCH-Interrupt-fast")));


void SysTick_init(void); //Systick初期化（delay_ms/delay_us）
void delay (int time); //割り込みタイマによる処理
//void delay_ms(int time_ms); //SysTickによるdelay
void delay_us(int time_us);
void delay_cnt(int cnt); //直接値を代入して使う（us以上に精度が欲しい場合に使用）

//-999 ~ 9999までを受け入れ
// それより大きい値or小さい値が入った場合はクリップ処理
void SegmentFlush_int (int num);
// 桁数により表示を変更
// 9999 ~ 1000
// 999.9 ~ 100.0
// 99.99 ~ 10.00
// 9.999 ~ 0.000
// もし9.35が入力されたら9.350を出力（必ず4桁で出力）
void SegmentFlush_Float (float num);

void SegmentFlush_HEX(uint16_t num); //16bit分のデータをHEX形式で出力

// セグメントを単独で点灯?消灯させる場合に使用
// Float関数を使うと無効になるので注意
//
//        ↓Dash
// 8.8.:8.'8.
//  ↑ ↑↑ ↑  ↑
//  4 3| 2  1 Dot
//     |
//     Coron
void SegmentDot1 (char Val);
void SegmentDot2 (char Val);
void SegmentDot3 (char Val);
void SegmentDot4 (char Val);
void SegmentDash (char Val);
void SegmentCoron (char Val);
// セグメントのデータを一括で消すための関数
// これを実行するとすべて消えるので注意
void SegmentClear (void);

int analogRead(int pin);

int Serial_LSensor();
int Serial_RSensor();
void Serial_MotorDrive_L(int power);
void Serial_MotorDrive_R(int power);
void Serial_MotorDrive(int l, int r);

//DotMatrix_t構造体のデータを送信
int Serial_DotMatrix_Write(DotMatrix_t data);
//登録された構造体がすでに送信済みか確認する関数
//送信されていない場合0を返却　送信されている場合は-1を返却
int DotMatrix_Data_Compare(DotMatrix_t data);


#endif /* USER_CH32V203_MYLIB_H_ */

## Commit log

2025-11-24 init Commit
2025-11-24 [Add] 回路図データ(ProgrammingKIT)の追加
2025-11-24 [Add] README.md (blank)
2025-11-25 変更を加えたblocklyduinoを追加
2025-11-25 Remove BlocklyDuino-v2 submodule
2025-11-27 [Add] オプション基板の基板データを追加
2025-11-27 [Rename] 回路図の名前変更
2025-11-27 [docs] README.mdの変更
2025-11-27 [Add] 書き込みプログラムの追加
2025-11-27 [docs] READMEの編集 ライセンス関係の追加
2025-11-27 add CITERA_BlocklyDuino
2025-11-27 [docs] LICENSE関係の追加
2025-11-27 [docs] 微小な修正
2025-11-28 [add] マイコン書き込みプログラムの追加
2025-11-28 [docs] README.mdの変更（テスト）
2025-11-28 [docs] README.mdの編集 - 導入方法の追記
2025-11-28 [docs] 微小な変更
2025-11-28 プログラミングツールの説明を追加
2025-11-28 プログラミングツールの説明の調整
2025-11-29 CITERA_BlocklyDuinoの一部更新
2025-11-30 [docs] 書き込み方法の追加

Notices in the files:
Circuit/Programming_Studie_Kit/Programming_Studie_Kit.kicad_sch:
©2025 CITERA
